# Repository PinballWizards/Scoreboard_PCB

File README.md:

# Scoreboard_PCB
Repo for the Scoreboard PCB KiCAD design docs

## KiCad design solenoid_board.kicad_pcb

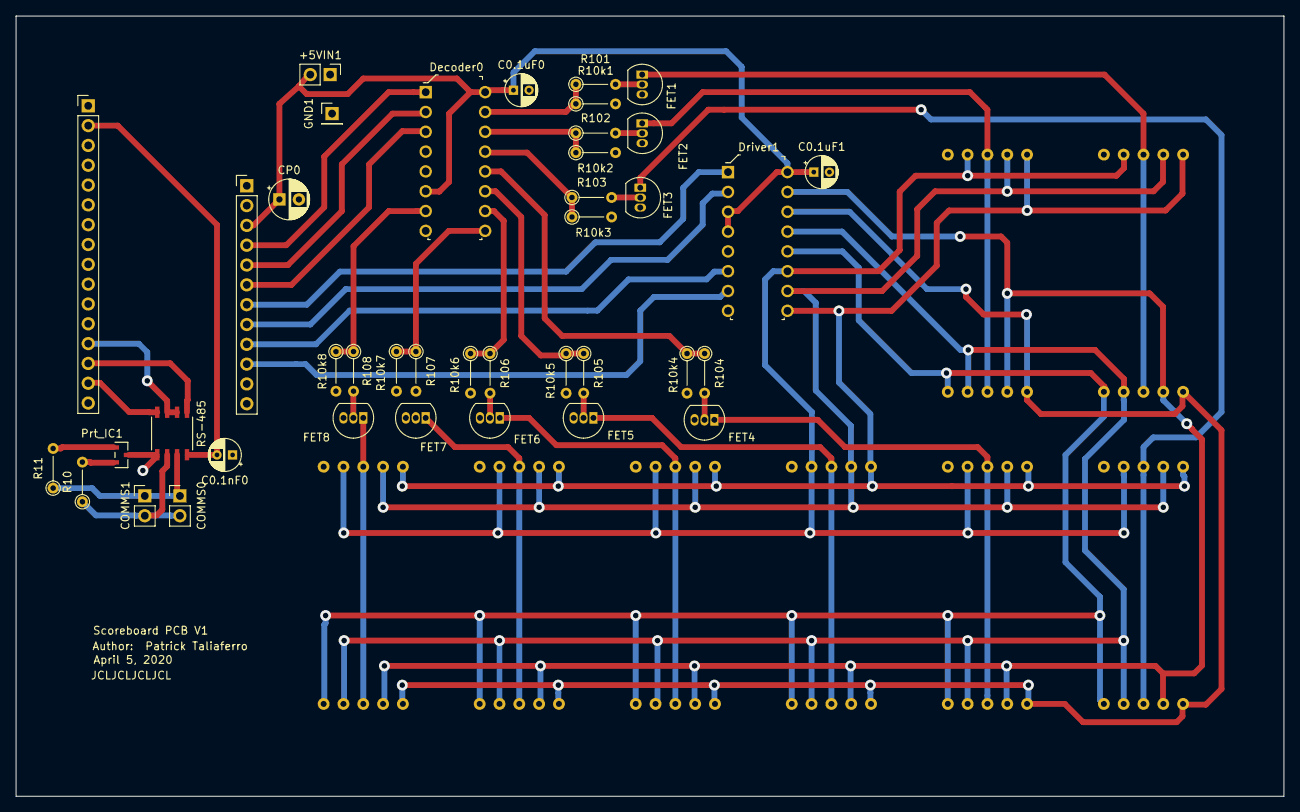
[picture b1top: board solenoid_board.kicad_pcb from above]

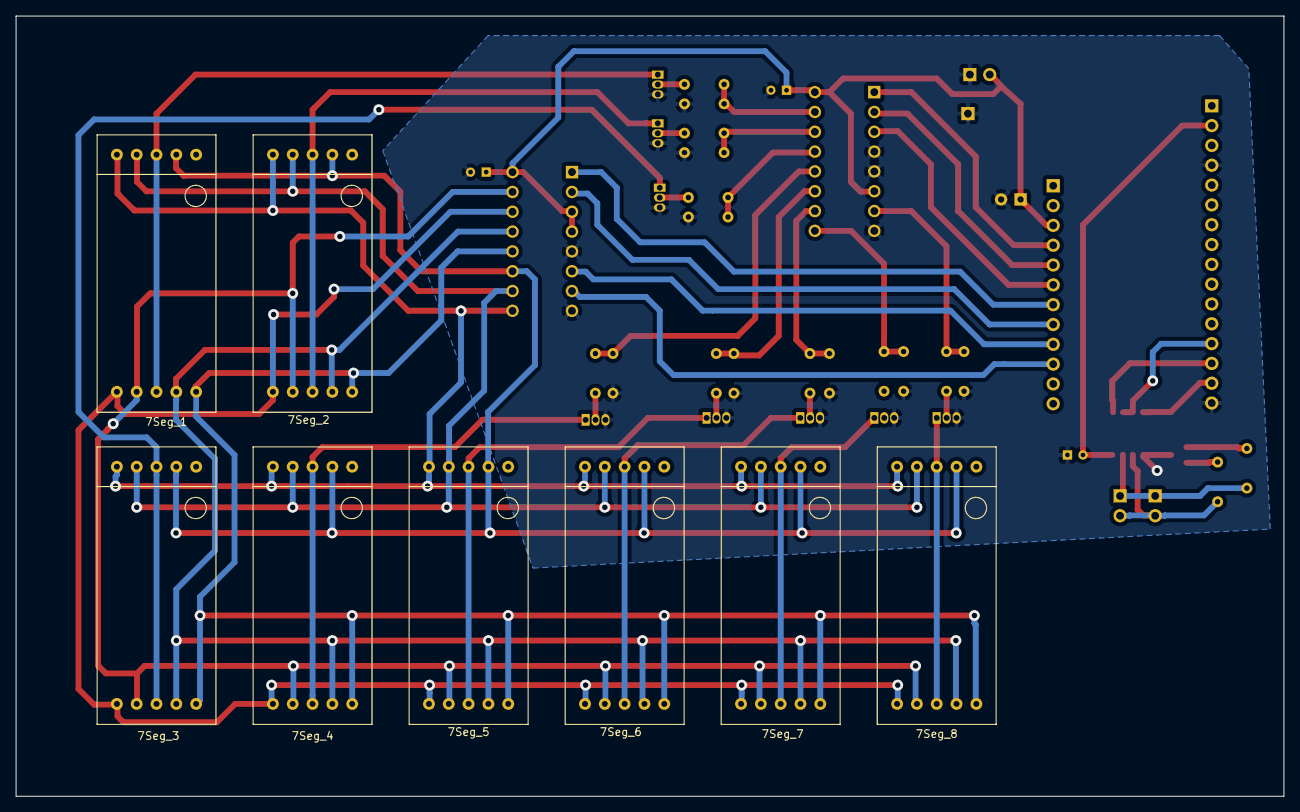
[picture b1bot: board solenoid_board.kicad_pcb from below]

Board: 2 copper layers, 162.5 x 100.0 mm, 48 parts (8 on the bottom side), 48 nets.

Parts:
7Seg_1, 7Seg_2, 7Seg_3, 7Seg_4, 7Seg_5, 7Seg_6, 7Seg_7, 7Seg_8: Conn_02x05_Top_Bottom; SC10-21SRWA
+5VIN1: Conn_01x02; PinHeader_1x02_P2.54mm_Vertical
C0.1nF0: 0.1 nF; CP_Radial_D4.0mm_P2.00mm
C0.1uF0, C0.1uF1: 0.1 uF; CP_Radial_D4.0mm_P2.00mm
COMMS0, COMMS1: Conn_01x02; PinHeader_1x02_P2.54mm_Vertical
CP0: CP; CP_Radial_D5.0mm_P2.50mm
Decoder0: Conn_02x08_Counter_Clockwise; DIP-16_W7.62mm
Driver1: Conn_02x08_Counter_Clockwise; DIP-16_W7.62mm
FET1, FET2, FET3, FET4, FET5, FET6, FET7, FET8: 2N7000; TO-92_Inline
GND1: Conn_01x01; PinHeader_1x01_P2.54mm_Vertical
J2: MCU_LEFT_LEGS; PinHeader_1x16_P2.54mm_Vertical
J3: MCU_RIGHT_LEGS; PinHeader_1x12_P2.54mm_Vertical
Prt_IC1: CDSOT23-SM712
R10, R11: 10; R_Axial_DIN0204_L3.6mm_D1.6mm_P5.08mm_Vertical
R10k1, R10k2, R10k3, R10k4, R10k5, R10k6, R10k7, R10k8: 10k; R_Axial_DIN0204_L3.6mm_D1.6mm_P5.08mm_Vertical
R101, R102, R103, R104, R105, R106, R107, R108: 100; R_Axial_DIN0204_L3.6mm_D1.6mm_P5.08mm_Vertical
RS-485: SN65HVD72DR

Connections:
+3V3: C0.1nF0.2, J2.2, RS-485.8
+5V: +5VIN1.2, C0.1uF0.1, C0.1uF1.1, CP0.1, Decoder0.6, Decoder0.16, Driver1.3, Driver1.4, Driver1.16, J3.3
/A: COMMS0.2, COMMS1.2, R10.1, RS-485.6
/B: COMMS0.1, COMMS1.1, R11.1, RS-485.7
/D5: Driver1.7, J3.10
/D6: Driver1.6, J3.9
/D9: Driver1.2, J3.8
/D10: Driver1.1, J3.7
/D11: Decoder0.3, J3.6
/D12: Decoder0.2, J3.5
/D13: Decoder0.1, J3.4
/Eighth_Display: 7Seg_8.3, 7Seg_8.8, FET8.1
/Fifth_Display: 7Seg_5.3, 7Seg_5.8, FET5.1
/First_Display: 7Seg_1.3, 7Seg_1.8, FET1.1
/Fourth_Display: 7Seg_4.3, 7Seg_4.8, FET4.1
/MISO: J2.13, RS-485.2, RS-485.3
/RX0: J2.14, RS-485.1
/Second_Display: 7Seg_2.3, 7Seg_2.8, FET2.1
/Seventh_Display: 7Seg_7.3, 7Seg_7.8, FET7.1
/Sixth_Display: 7Seg_6.3, 7Seg_6.8, FET6.1
/TX1: J2.15, RS-485.4
/Third_Display: 7Seg_3.3, 7Seg_3.8, FET3.1
/Y0: Decoder0.15, R10k1.1, R101.1
/Y1: Decoder0.14, R10k2.1, R102.1
/Y2: Decoder0.13, R10k3.1, R103.1
/Y3: Decoder0.12, R10k4.1, R104.1
/Y4: Decoder0.11, R10k5.1, R105.1
/Y5: Decoder0.10, R10k6.1, R106.1
/Y6: Decoder0.9, R10k7.1, R107.1
/Y7: Decoder0.7, R10k8.1, R108.1
/a: 7Seg_1.7, 7Seg_2.7, 7Seg_3.7, 7Seg_4.7, 7Seg_5.7, 7Seg_6.7, 7Seg_7.7, 7Seg_8.7, Driver1.13
/b: 7Seg_1.6, 7Seg_2.6, 7Seg_3.6, 7Seg_4.6, 7Seg_5.6, 7Seg_6.6, 7Seg_7.6, 7Seg_8.6, Driver1.12
/c: 7Seg_1.4, 7Seg_2.4, 7Seg_3.4, 7Seg_4.4, 7Seg_5.4, 7Seg_6.4, 7Seg_7.4, 7Seg_8.4, Driver1.11
/d: 7Seg_1.2, 7Seg_2.2, 7Seg_3.2, 7Seg_4.2, 7Seg_5.2, 7Seg_6.2, 7Seg_7.2, 7Seg_8.2, Driver1.10
/e: 7Seg_1.1, 7Seg_2.1, 7Seg_3.1, 7Seg_4.1, 7Seg_5.1, 7Seg_6.1, 7Seg_7.1, 7Seg_8.1, Driver1.9
/f: 7Seg_1.9, 7Seg_2.9, 7Seg_3.9, 7Seg_4.9, 7Seg_5.9, 7Seg_6.9, 7Seg_7.9, 7Seg_8.9, Driver1.15
/g: 7Seg_1.10, 7Seg_2.10, 7Seg_3.10, 7Seg_4.10, 7Seg_5.10, 7Seg_6.10, 7Seg_7.10, 7Seg_8.10, Driver1.14
GND: +5VIN1.1, C0.1nF0.1, C0.1uF0.2, C0.1uF1.2, CP0.2, Decoder0.4, Decoder0.5, Decoder0.8, Driver1.5, Driver1.8, FET1.3, FET2.3, FET3.3, FET4.3, FET5.3, FET6.3, FET7.3, FET8.3, GND1.1, J2.4, J2.16, Prt_IC1.3, R10k1.2, R10k2.2, R10k3.2, R10k4.2, R10k5.2, R10k6.2, R10k7.2, R10k8.2, RS-485.5
unnamed: FET1.2, R101.2
unnamed: FET2.2, R102.2
unnamed: FET3.2, R103.2
unnamed: FET4.2, R104.2
unnamed: FET5.2, R105.2
unnamed: FET6.2, R106.2
unnamed: FET7.2, R107.2
unnamed: FET8.2, R108.2
unnamed: Prt_IC1.1, R11.2
unnamed: Prt_IC1.2, R10.2

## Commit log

2020-02-10 Sourced a 7-Segment Display and drafted a schematic for a LED matrix with 9 displays.
2020-02-10 Changed Geometry of PCB, removed edges, cleaned up displays. Next steps: routing.
2020-02-11 Changed 2-pin terminal block and 7-Segment display suppliers on the BOM. This shaved 30% off the original per-board price.
2020-02-11 Changed resistor footprints, changed resistor supplier. Still need to route wires.
2020-02-12 Worked on Geometry of board. Needs to be finalized.
2020-02-12 Rearranged Component Geometry, switched out Transciever Resistor footprints, Routed Some wires.
2020-02-13 Finished Routing and generated new .gbr files. I am unsatisfied with the size of the board, and the geometry may need to be moved around to allow ball count to be displayed underneath the score.
2020-02-13 Added Mounting Holes
2020-02-14 Deleted all the wire routes related to the scoreboard.
2020-02-24 Changed BOM, changed Schematic symbols/footprints. Still need to add mosfets and ICs.
2020-02-24 Major revisions occurred to the Schematic. Sourced 7-Segment display and MosFETs.
2020-02-24 Schematic Finished. Need to figure out geometry and route layout.
2020-02-25 Serious Geometry design occurred.
2020-02-25 Worked Geometry to 40% mark.
2020-02-25 Changed Geometry significantly.
2020-03-14 Revised Schematic based on Dr. Fuch's suggested edits. Need to finalize Geometry and update BOM.
2020-04-05 Finished laying out Scoreboard PCB, good enough for government work.

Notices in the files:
parts and their libraries:
Copyright 2016 Accelerated Designs. All rights reserved.
